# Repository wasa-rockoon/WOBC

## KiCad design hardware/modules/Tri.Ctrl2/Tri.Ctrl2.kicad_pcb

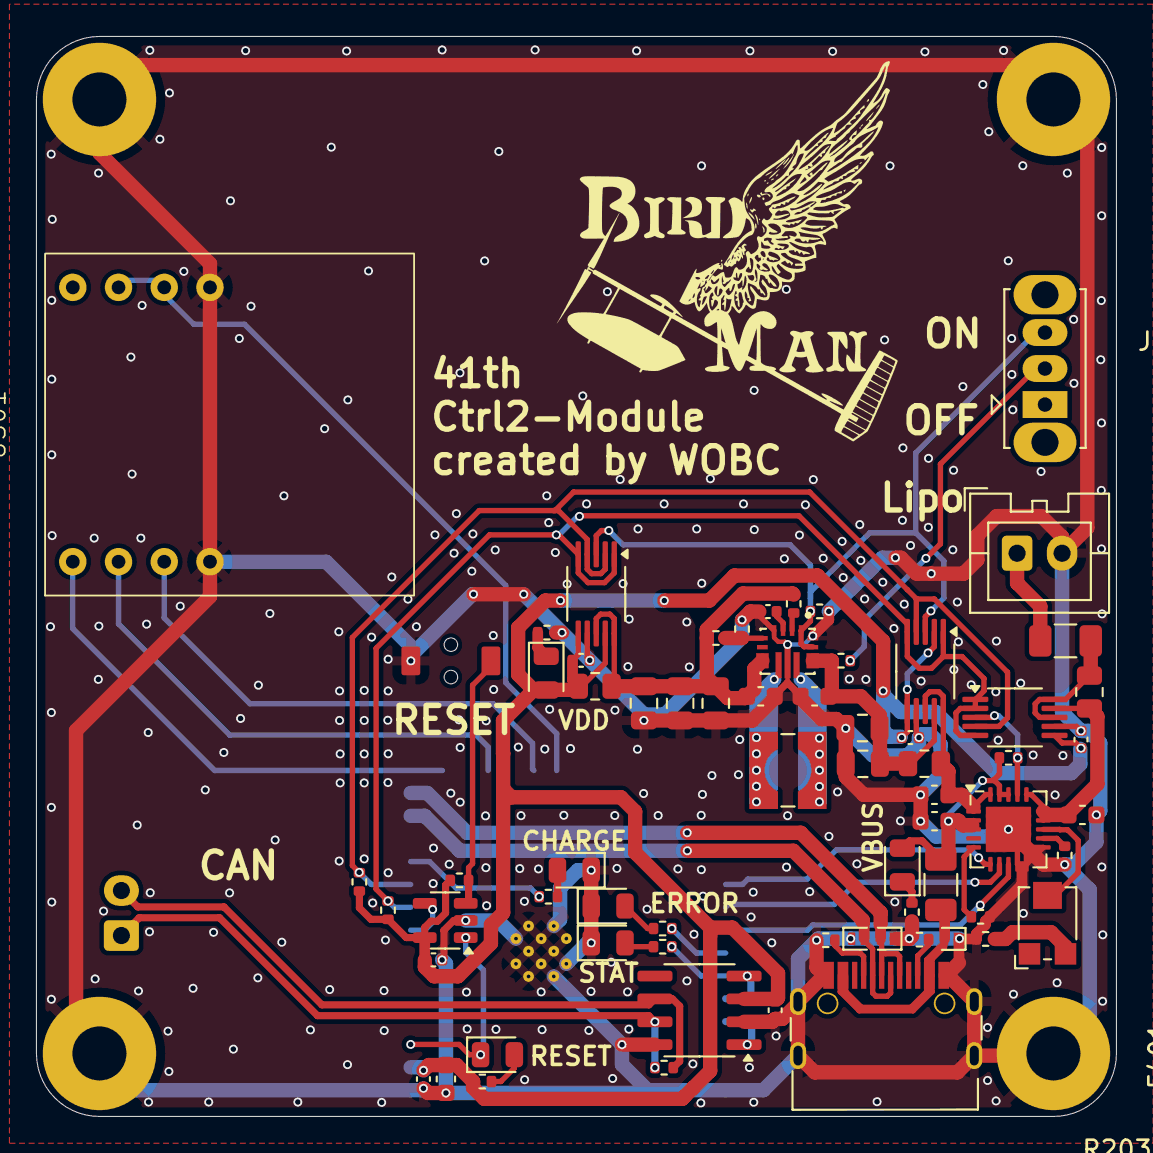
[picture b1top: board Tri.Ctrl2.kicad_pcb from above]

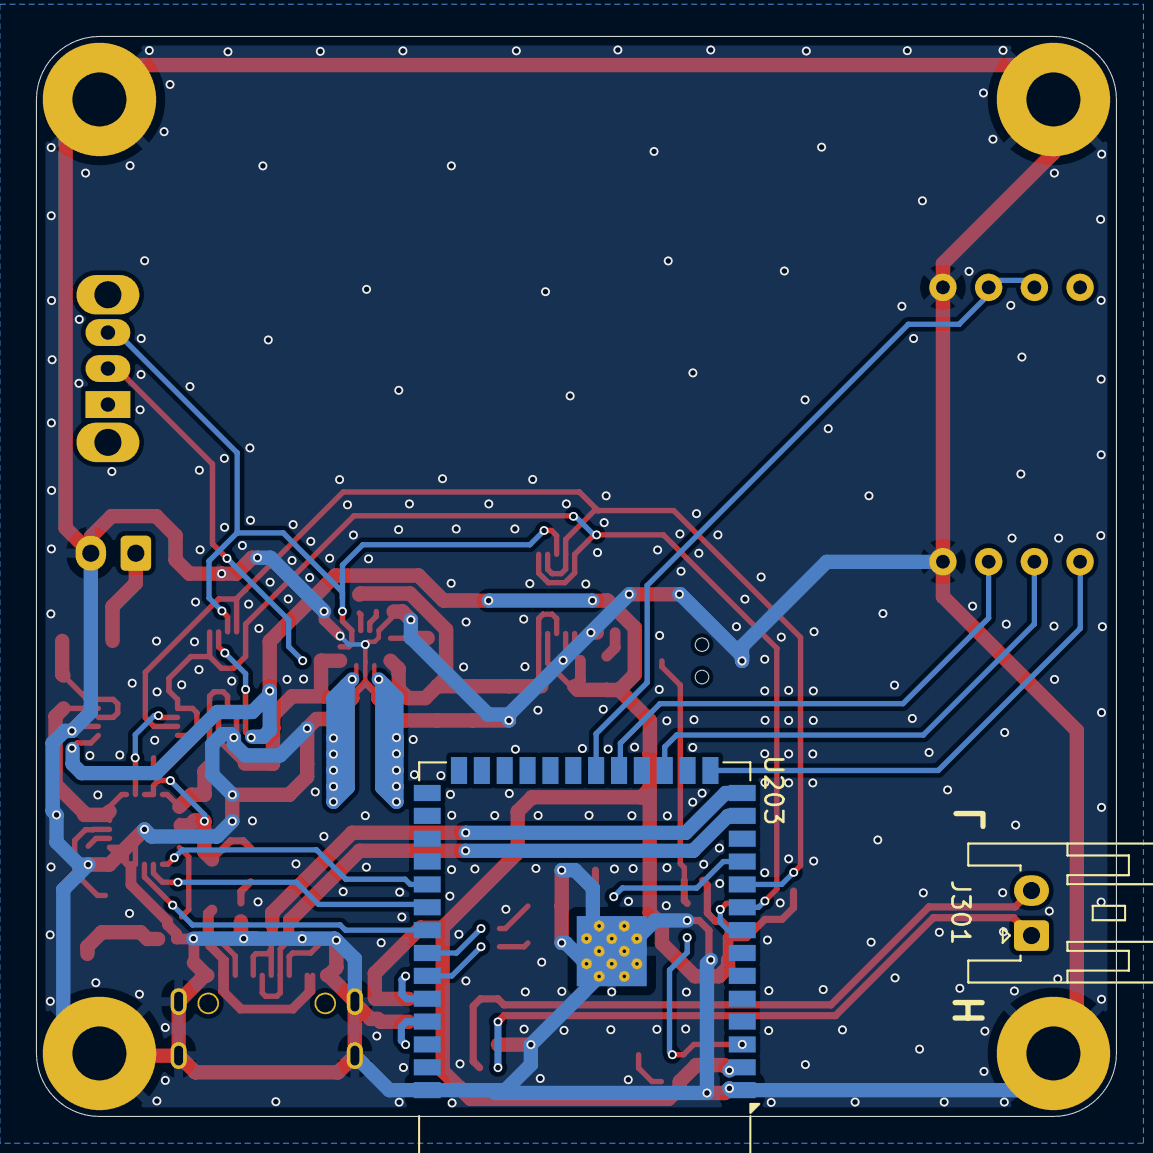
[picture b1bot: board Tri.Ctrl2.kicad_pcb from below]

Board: 2 copper layers, 60.0 x 60.0 mm, 70 parts (2 on the bottom side), 51 nets.

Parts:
B101: Board_1U_60x60
C201, C202, C204, C402, C407, C409, C414: 100nF; C_0402_1005Metric
C203, C401, C403, C404, C408, C410: 10uF; C_0603_1608Metric
C405, C406, C411, C412, C413: 22uF; C_0805_2012Metric
D201, D202, D203: 5V; D_SOD-882
D204: RESET; LED_0805_2012Metric
D205: ERROR; LED_0805_2012Metric
D206: STAT; LED_0805_2012Metric
F401, F402: Polyfuse; Fuse_1206_3216Metric
J301: Conn_01x02_Pin; JST_XA_S02B-XASK-1N-BN_1x02_P2.50mm_Horizontal
J401: LiPo; JST_XA_B02B-XASK-1_1x02_P2.50mm_Vertical
L401: L; L_Wuerth_WE-TPC-3816
LED401: USB Power; LED_0805_2012Metric
LED402: CHARGE; LED_0805_2012Metric
LED403: VDD; LED_0805_2012Metric
R201, R206, R208, R405, R408: 10k; R_0402_1005Metric
R202, R203: 5.1k; R_0402_1005Metric
R204, R205, R207: 470; R_0402_1005Metric
R301: 120; R_0402_1005Metric
R401, R402, R403, R415: 1k; R_0402_1005Metric
R404, R406, R411: 100k; R_0402_1005Metric
R407, R410, R414: 50mΩ; R_0805_2012Metric
R409: 330k; R_0402_1005Metric
R412: 15k; R_0402_1005Metric
R413: 47k; R_0402_1005Metric
RV401: 10k; Potentiometer_Bourns_TC33X_Vertical
SW201: RESET_sw; TVAF06-A020B-R
SW401: Power Switch; SW_Slide_SPDT_Straight_CK_OS102011MS2Q
U201: TPS3820; SOT-23-5
U202: SN65HVD230; SOIC-8_3.9x4.9mm_P1.27mm
U203: ESP32-S3-WROOM-1
U401: MCP73871-1CC; QFN-20-1EP_4x4mm_P0.5mm_EP2.5x2.5mm
U402, U403, U405: INA226; VSSOP-10_3x3mm_P0.5mm
U404: TPS63070RNMR; VREG_TPS63070RNMR
U501: ICS
USB201: USB_C_Receptacle_USB2.0; USB_C_TYPEC-301S-ACP16X7

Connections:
/CANH: J301.1, R301.2, U202.7 (CANH)
/CANL: J301.2, R301.1, U202.6 (CANL)
/ESP32Core/CAN_RX: U202.4 (R), U203.36 (U0RXD/GPIO44/CLK_OUT2)
/ESP32Core/CAN_TX: U202.1 (D), U203.37 (U0TXD/GPIO43/CLK_OUT1)
/ESP32Core/GPIO11: U203.19 (GPIO11/TOUCH11/ADC2_CH0/FSPID/FSPIIO5/S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), U501.3 (EN_IN)
/ESP32Core/GPIO12: U203.20 (GPIO12/TOUCH12/ADC2_CH1/FSPICLK/FSPIIO6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), U501.5 (IOREF), U501.6 (IOREF2)
/ESP32Core/GPIO18: R402.2, U203.11 (GPIO18/U1RXD/ADC2_CH7/CLK_OUT3)
/ESP32Core/USB_D+: D202.2 (A2), U203.14 (GPIO20/U1CTS/ADC2_CH9/CLK_OUT1/USB_D+), USB201.A6 (D+), USB201.B6 (D+)
/ESP32Core/USB_D-: D203.2 (A2), U203.13 (GPIO19/U1RTS/ADC2_CH8/CLK_OUT2/USB_D-), USB201.A7 (D-), USB201.B7 (D-)
/ESP32Core/WDI: U201.4 (WDI), U203.8 (GPIO15/U0RTS/ADC2_CH4/XTAL_32K_P)
/PG: U203.31 (GPIO38/FSPIWP/SUBSPIWP), U401.6 (~PG)
/Power/PROG: RV401.2, U401.13 (PROG1)
/RX: U203.17 (GPIO9/TOUCH9/ADC1_CH8/FSPIHD/SUBSPIHD), U501.2 (RX)
/SCL: R206.2, U203.9 (GPIO16/U0CTS/ADC2_CH5/XTAL_32K_N), U402.1 (A1), U402.5 (SCL), U403.1 (A1), U403.2 (A0), U403.5 (SCL), U405.1 (A1), U405.5 (SCL)
/SDA: R208.2, U203.10 (GPIO17/U1TXD/ADC2_CH6), U402.4 (SDA), U403.4 (SDA), U405.2 (A0), U405.4 (SDA)
/STAT1: U203.33 (MTDO/GPIO40/CLK_OUT2), U401.8 (STAT1/~LBO)
/STAT2: U203.32 (MTCK/GPIO39/CLK_OUT3/SUBSPICS1), U401.7 (STAT2)
/TX: U203.15 (GPIO3/TOUCH3/ADC1_CH2), U501.1 (TX)
GND: B101.GND, C201.1, C202.1, C203.1, C204.2, C401.2, C402.2, C403.2, C404.2, C405.2, C406.2, C407.2, C408.2, C409.2, C410.2, C411.2, C412.2, C413.2, C414.2, D201.1 (A1), D202.1 (A1), D203.1 (A1), D205.1 (K), D206.1 (K), J401.2, LED402.1 (K), R202.2, R203.2, R401.2, R403.2, R404.2, R405.2, R409.2, R412.1, R415.2, SW201.2, U201.2 (GND), U202.2 (GND), U202.8 (Rs), U203.1 (GND), U203.40 (GND), U203.41 (GND), U401.9 (~TE), U401.10 (V_{SS}), U401.11 (V_{SS}), U401.21 (V_{SS}), U402.7 (GND), U403.7 (GND), U404.4 (GND), U404.10 (PGND), U404.15 (VSEL), U405.7 (GND), U501.7 (GND), U501.8 (GND), USB201.A1 (GND), USB201.A12 (GND), USB201.B1 (GND), USB201.B12 (GND), USB201.S1 (SHIELD)
unnamed: D204.2 (A), R204.2
unnamed: D205.2 (A), R205.2
unnamed: D206.2 (A), R207.2
unnamed: F402.2, J401.1
unnamed: C401.1, F401.2, LED401.2 (A), R406.1, U401.2 (VPCC), U401.3 (SEL), U401.18 (IN), U401.19 (IN)
unnamed: LED401.1 (K), R401.1
unnamed: LED402.2 (A), R402.1
unnamed: LED403.1 (K), R415.1
unnamed: R403.1, RV401.3
unnamed: R408.1, SW401.2 (B)
unnamed: R409.1, SW401.3 (C), U402.3 (~Alert), U404.1 (PS/SYNC), U404.14 (EN), U405.3 (~Alert)
unnamed: R201.2, SW201.1, U201.3 (MR)
unnamed: R205.1, U203.34 (MTDI/GPIO41/CLK_OUT1)
unnamed: R207.1, U203.35 (MTMS/GPIO42)
unnamed: R406.2, U401.17 (CE), U403.3 (~Alert)
unnamed: R404.1, U401.12 (PROG3)
unnamed: R405.1, U401.5 (THERM)
unnamed: C404.1, R410.1, U401.14 (V_{BAT}), U401.15 (V_{BAT}), U401.16 (V_{BAT_SENSE}), U403.9 (Vin-)
unnamed: C403.1, R407.1, U401.1 (OUT), U401.20 (OUT), U402.8 (Vbus), U402.10 (Vin+)
unnamed: C405.1, C406.1, C408.1, R407.2, R408.2, U402.9 (Vin-), U404.12_13 (VIN)
unnamed: F402.1, R410.2, U403.8 (Vbus), U403.10 (Vin+)
unnamed: R412.2, R413.1, U404.5 (FB)
unnamed: L401.1, U404.11 (L1)
unnamed: L401.2, U404.9 (L2)
unnamed: R411.2, U404.2 (PG)
unnamed: C409.1, U404.3 (VAUX)
unnamed: C410.1, C411.1, C412.1, C413.1, R411.1, R413.2, R414.1, U404.7_8 (VOUT), U405.8 (Vbus), U405.10 (Vin+)
unnamed: R202.1, USB201.A5 (CC1)
unnamed: R203.1, USB201.B5 (CC2)
RESET: D204.1 (K), U201.1 (RESET), U203.3 (EN)
VBUS: D201.2 (A2), F401.1, USB201.A4 (VBUS), USB201.A9 (VBUS), USB201.B4 (VBUS), USB201.B9 (VBUS)
VDD: C201.2, C202.2, C203.2, C204.1, C402.1, C407.1, C414.1, LED403.2 (A), R201.1, R204.1, R206.1, R208.1, R414.2, U201.5 (VDD), U202.3 (VCC), U203.2 (3V3), U402.2 (A0), U402.6 (VS), U403.6 (VS), U405.6 (VS), U405.9 (Vin-)

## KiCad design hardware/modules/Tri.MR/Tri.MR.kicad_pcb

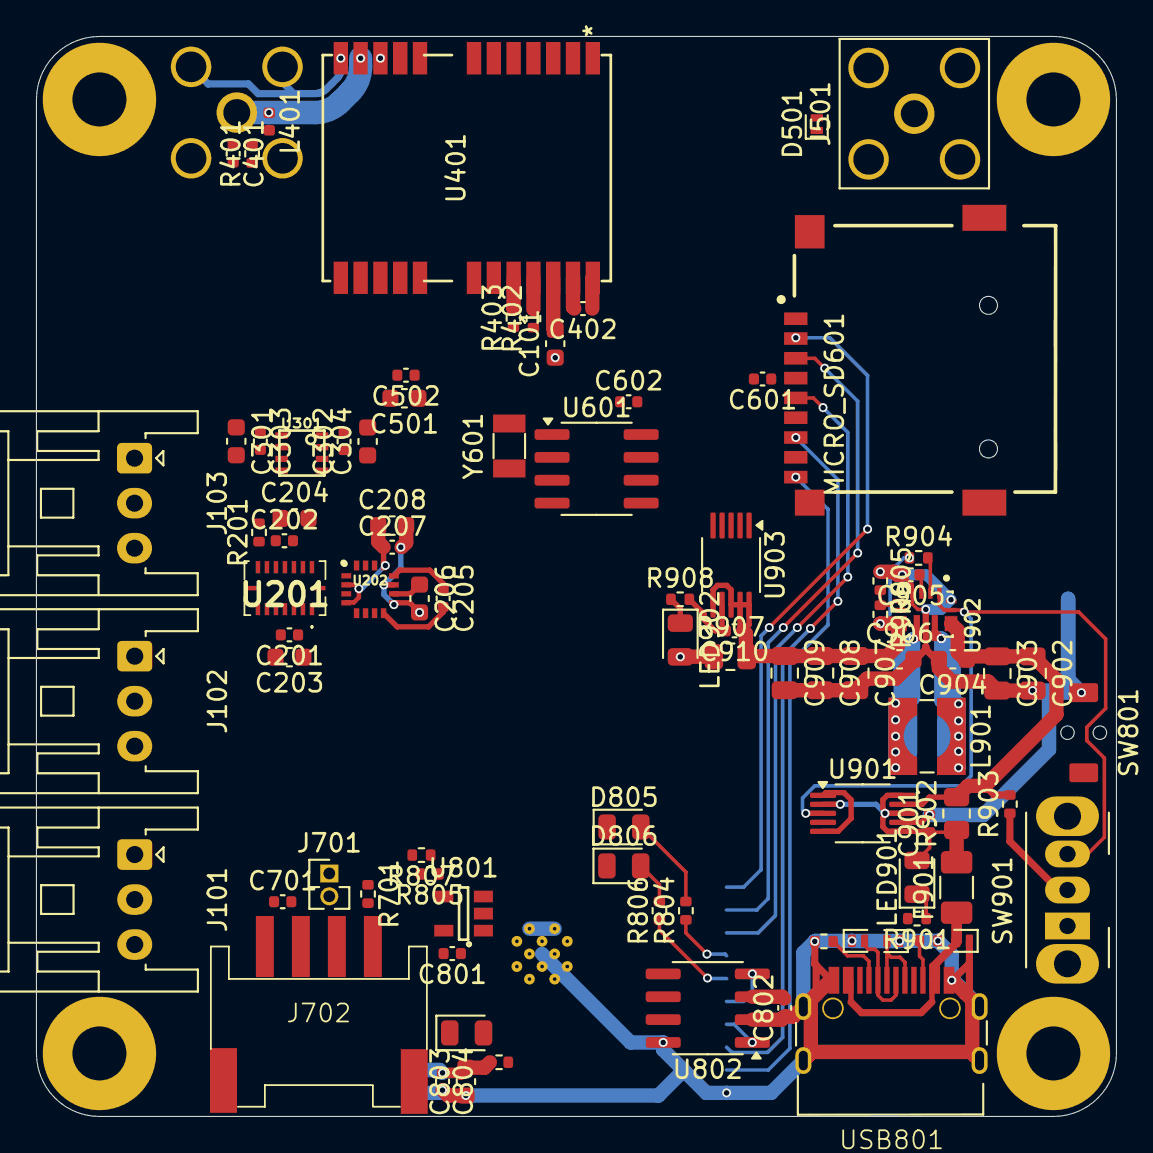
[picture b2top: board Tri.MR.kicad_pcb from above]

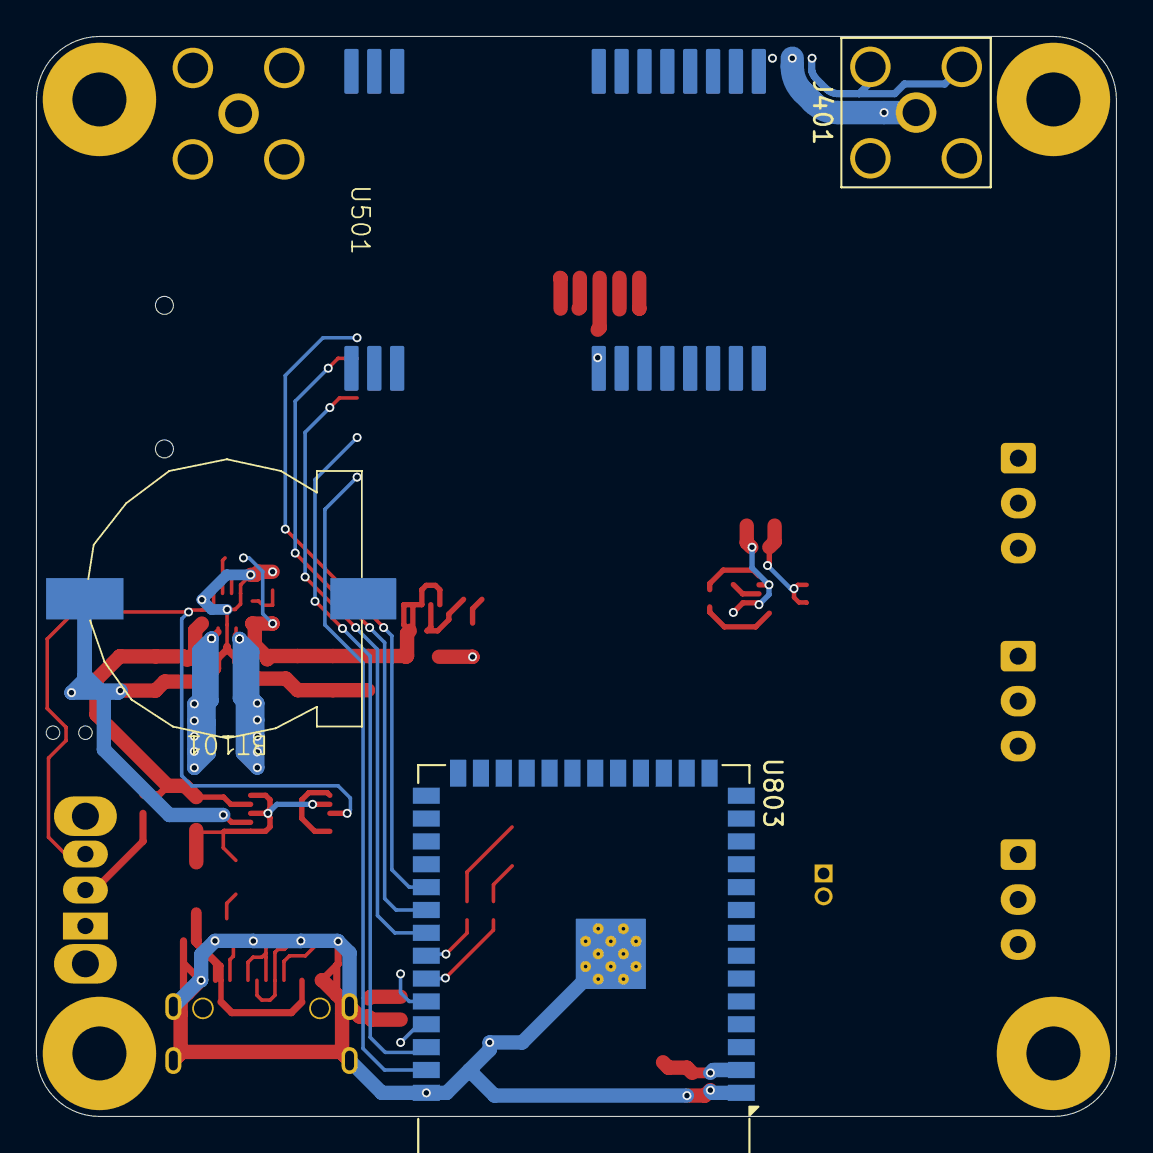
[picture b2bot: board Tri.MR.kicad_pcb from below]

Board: 2 copper layers, 60.0 x 60.0 mm, 92 parts (4 on the bottom side), 62 nets.

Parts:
B101: Board_1U_60x60
BT101: Battery; cr1220
C101, C803, C904, C906: 10uF; C_0603_1608Metric
C201, C202, C207, C302, C303, C401, C402, C602, C701, C801, C802, C804, C901, C905, C910: 100nF; C_0402_1005Metric
C203, C204, C208, C301, C304: 10μF; C_0603_1608Metric
C205: 0.22μF; C_0402_1005Metric
C206: 4.7μF; C_0603_1608Metric
C501: 10u; C_0603_1608Metric
C502: 100n; C_0402_1005Metric
C601: 10uF; C_0402_1005Metric
C902, C903, C907, C908, C909: 22uF; C_0805_2012Metric
D501: ESD9B5.0ST5G; D_SOD-882
D801, D802, D803: 5V; D_SOD-882
D804: RESET; LED_0805_2012Metric
D805: ERROR; LED_0805_2012Metric
D806: STAT; LED_0805_2012Metric
F901: Polyfuse; Fuse_1206_3216Metric
J101: hight; JST_XA_S03B-XASK-1N-BN_1x03_P2.50mm_Horizontal
J102: pera; JST_XA_S03B-XASK-1N-BN_1x03_P2.50mm_Horizontal
J103: airspeed; JST_XA_S03B-XASK-1N-BN_1x03_P2.50mm_Horizontal
J401, J501: SMA; SMA_Amphenol_132203-12_Horizontal
J701: Jumper; PinHeader_1x02_P1.27mm_Vertical
J702: Conn_01x04_MountingPin; Grove_4P_L_SMD
L401: 27nH, 300mA; L_0402_1005Metric
L901: L; L_Wuerth_WE-TPC-3816
LED901: USB Power; LED_0805_2012Metric
LED902: VDD; LED_0805_2012Metric
MICRO_SD601: TF-01A
R201: 4.7K; R_0402_1005Metric
R401: 10; R_0402_1005Metric
R402, R403: 33; R_0402_1005Metric
R701: 120; R_0402_1005Metric
R801, R802: 5.1k; R_0402_1005Metric
R803, R804, R806: 470; R_0402_1005Metric
R805, R807, R903: 10k; R_0402_1005Metric
R901, R908: 1k; R_0402_1005Metric
R902, R907: 50mΩ; R_0805_2012Metric
R904: 100k; R_0402_1005Metric
R905: 15k; R_0402_1005Metric
R906: 47k; R_0402_1005Metric
SW801: RESET_sw; TVAF06-A020B-R
SW901: Power Switch; SW_Slide_SPDT_Angled_CK_OS102011MA1Q
U201: BMI088
U202: QMC5883L; _HMC5883L
U301: BME280
U401: NEO-M9N-00B; ATGM332D-5N31
U501: E220-900T22S(JP)
U601: PCF8563T; SOIC-8_3.9x4.9mm_P1.27mm
U801: TPS3820; SOT_23_5
U802: SN65HVD230; SOIC-8_3.9x4.9mm_P1.27mm
U803: ESP32-S3-WROOM-1
U901, U903: INA226; VSSOP-10_3x3mm_P0.5mm
U902: TPS63070RNMR; VREG_TPS63070RNMR
USB801: USB_C_Receptacle_USB2.0; USB_C_TYPEC-301S-ACP16X7
Y601: Crystal; Crystal_SMD_3215-2Pin_3.2x1.5mm

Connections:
/AUX: U501.9 (AUX), U803.17 (GPIO9/TOUCH9/ADC1_CH8/FSPIHD/SUBSPIHD)
/CLK: MICRO_SD601.5 (CLK), U803.33 (MTDO/GPIO40/CLK_OUT2)
/DET: MICRO_SD601.CD1 (CD), U803.39 (GPIO1/TOUCH1/ADC1_CH0)
/ESP32S3/CANH: J702.1, R701.2, U802.7 (CANH)
/ESP32S3/CANL: J701.2, J702.2, U802.6 (CANL)
/ESP32S3/CAN_RX: U802.4 (R), U803.36 (U0RXD/GPIO44/CLK_OUT2)
/ESP32S3/CAN_TX: U802.1 (D), U803.37 (U0TXD/GPIO43/CLK_OUT1)
/ESP32S3/USB_D+: D802.2 (A2), U803.14 (GPIO20/U1CTS/ADC2_CH9/CLK_OUT1/USB_D+), USB801.A6 (D+), USB801.B6 (D+)
/ESP32S3/USB_D-: D803.2 (A2), U803.13 (GPIO19/U1RTS/ADC2_CH8/CLK_OUT2/USB_D-), USB801.A7 (D-), USB801.B7 (D-)
/ESP32S3/VUSB: D801.2 (A2), F901.1, USB801.A4 (VBUS), USB801.A9 (VBUS), USB801.B4 (VBUS), USB801.B9 (VBUS)
/ESP32S3/WDI: U801.4 (WDI), U803.8 (GPIO15/U0RTS/ADC2_CH4/XTAL_32K_P)
/M0: U501.5 (M0), U803.21 (GPIO13/TOUCH13/ADC2_CH2/FSPIQ/FSPIIO7/S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)
/M1: U501.6 (M1), U803.20 (GPIO12/TOUCH12/ADC2_CH1/FSPICLK/FSPIIO6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)
/MIOS: MICRO_SD601.7 (DAT0), U803.38 (GPIO2/TOUCH2/ADC1_CH1)
/MOSI: MICRO_SD601.3 (CMD), U803.32 (MTCK/GPIO39/CLK_OUT3/SUBSPICS1)
/RESET: U401.8 (RESET_N), U803.25 (GPIO48/SPICLK_N/SUBSPICLK_N_DIFF)
/RTX: U501.8 (TXD), U803.18 (GPIO10/TOUCH10/ADC1_CH9/FSPICS0/FSPIIO4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)
/RX: R402.1, U803.23 (GPIO21)
/SCL: R805.2, U201.8 (SCL/SCK), U202.1 (SCL), U301.4 (SCK), U601.6 (SCL), U803.9 (GPIO16/U0CTS/ADC2_CH5/XTAL_32K_N), U901.1 (A1), U901.5 (SCL), U903.1 (A1), U903.5 (SCL)
/SDA: R807.2, U201.9 (SDA/SDI), U202.16 (SDA), U301.3 (SDI), U601.5 (SDA), U803.10 (GPIO17/U1TXD/ADC2_CH6), U901.4 (SDA), U903.2 (A0), U903.4 (SDA)
/SS: MICRO_SD601.2 (CD/DAT3), U803.31 (GPIO38/FSPIWP/SUBSPIWP)
/TIMEPULSE: U401.3 (TIMEPULSE), U803.24 (GPIO47/SPICLK_P/SUBSPICLK_P_DIFF)
/TRX: U501.7 (RXD), U803.19 (GPIO11/TOUCH11/ADC2_CH0/FSPID/FSPIIO5/S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)
/TX: R403.1, U803.22 (GPIO14/TOUCH14/ADC2_CH3/FSPIWP/FSPIDQS/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)
/airspeed: J103.1, U803.6 (GPIO6/TOUCH6/ADC1_CH5)
/hight: J101.1, U803.4 (GPIO4/TOUCH4/ADC1_CH3)
/pera: J102.1, U803.5 (GPIO5/TOUCH5/ADC1_CH4)
GND: B101.GND, BT101.2 (-), C101.1, C201.2, C202.2, C203.2, C204.2, C206.2, C207.2, C208.2, C301.2, C302.2, C303.2, C304.2, C401.2, C402.1, C501.2, C502.2, C601.2, C602.1, C701.1, C801.1, C802.1, C803.1, C804.2, C901.2, C902.2, C903.2, C904.2, C905.2, C906.2, C907.2, C908.2, C909.2, C910.2, D501.1 (A1), D801.1 (A1), D802.1 (A1), D803.1 (A1), D805.1 (K), D806.1 (K), J101.3, J102.3, J103.3, J401.2 (Ext), J501.2 (Ext), J702.4, J702.MP (MountPin), MICRO_SD601.6 (VSS), MICRO_SD601.MP1 (SHIELD), MICRO_SD601.MP2 (SHIELD), MICRO_SD601.MP3 (SHIELD), MICRO_SD601.MP4 (SHIELD), R801.2, R802.2, R901.2, R905.1, R908.2, SW801.2, U201.4 (GNDA), U201.6 (GNDIO), U202.9 (GND), U202.11 (GND), U301.1 (GND), U301.5 (SDO), U301.7 (GND), U401.10 (GND), U401.12 (GND), U401.13 (GND), U401.24 (GND), U501.1 (GND), U501.2 (GND), U501.3 (GND), U501.4 (GND), U501.11 (GND), U501.13 (GND), U501.19 (GND), U501.20 (GND), U501.22 (GND), U601.4 (VSS), U801.2 (GND), U802.2 (GND), U802.8 (Rs), U803.1 (GND), U803.40 (GND), U803.41 (GND), U901.7 (GND), U902.4 (GND), U902.10 (PGND), U902.15 (VSEL), U903.7 (GND), USB801.A1 (GND), USB801.A12 (GND), USB801.B1 (GND), USB801.B12 (GND), USB801.S1 (SHIELD)
GPS_ANT1: J401.1 (In), L401.1, U401.11 (RF_IN)
GPS_Backup: BT101.1 (+), C101.2, U401.22 (V_BCKP)
unnamed: C401.1, L401.2, R401.2
unnamed: D501.2 (A2), J501.1 (In), U501.21 (ANT)
unnamed: D804.2 (A), R803.2
unnamed: D805.2 (A), R804.2
unnamed: D806.2 (A), R806.2
unnamed: J701.1, R701.1
unnamed: LED901.1 (K), R901.1
unnamed: LED902.1 (K), R908.1
unnamed: R903.1, SW901.2 (B)
unnamed: SW901.3 (C), U901.3 (~Alert), U902.1 (PS/SYNC), U902.14 (EN), U903.3 (~Alert)
unnamed: R201.1, U201.10 (SDO2), U201.15 (SDO1)
unnamed: C206.1, U202.10 (C1)
unnamed: C205.1, U202.12 (SETC)
unnamed: C205.2, U202.8 (STEP)
unnamed: R402.2, U401.21 (RXD_/_SPI_MOSI)
unnamed: R403.2, U401.20 (TXD_/_SPI_MISO)
unnamed: U601.1 (OSCI), Y601.1
unnamed: U601.2 (OSCO), Y601.2
unnamed: SW801.1, U801.3 (MR)
unnamed: R804.1, U803.34 (MTDI/GPIO41/CLK_OUT1)
unnamed: R806.1, U803.35 (MTMS/GPIO42)
unnamed: C902.1, C903.1, C904.1, R902.2, R903.2, U901.9 (Vin-), U902.12_13 (VIN)
unnamed: R905.2, R906.1, U902.5 (FB)
unnamed: L901.1, U902.11 (L1)
unnamed: L901.2, U902.9 (L2)
unnamed: R904.2, U902.2 (PG)
unnamed: C905.1, U902.3 (VAUX)
unnamed: R801.1, USB801.A5 (CC1)
unnamed: R802.1, USB801.B5 (CC2)
RESET: D804.1 (K), U801.1 (RESET), U803.3 (EN)
VDD: C201.1, C202.1, C203.1, C204.1, C207.1, C208.1, C301.1, C302.1, C303.1, C304.1, C402.2, C501.1, C502.1, C601.1, C602.2, C701.2, C801.2, C802.2, C803.2, C804.1, C906.1, C907.1, C908.1, C909.1, C910.1, J101.2, J102.2, J103.2, J702.3, LED902.2 (A), MICRO_SD601.4 (VDD), R201.2, R803.1, R805.1, R807.1, R904.1, R906.2, R907.1, R907.2, U201.3 (VDD), U201.7 (PS), U201.11 (VDDIO), U202.2 (VDD), U202.4 (S1), U202.13 (VDDIO), U301.2 (CSB), U301.6 (VDDIO), U301.8 (VDD), U401.7 (V_USB), U401.23 (VCC), U501.10 (VDD), U601.8 (VDD), U801.5 (VDD), U802.3 (VCC), U803.2 (3V3), U902.7_8 (VOUT), U903.6 (VS), U903.8 (Vbus), U903.9 (Vin-), U903.10 (Vin+)
VPP: C901.1, F901.2, LED901.2 (A), R902.1, U901.2 (A0), U901.6 (VS), U901.8 (Vbus), U901.10 (Vin+)
